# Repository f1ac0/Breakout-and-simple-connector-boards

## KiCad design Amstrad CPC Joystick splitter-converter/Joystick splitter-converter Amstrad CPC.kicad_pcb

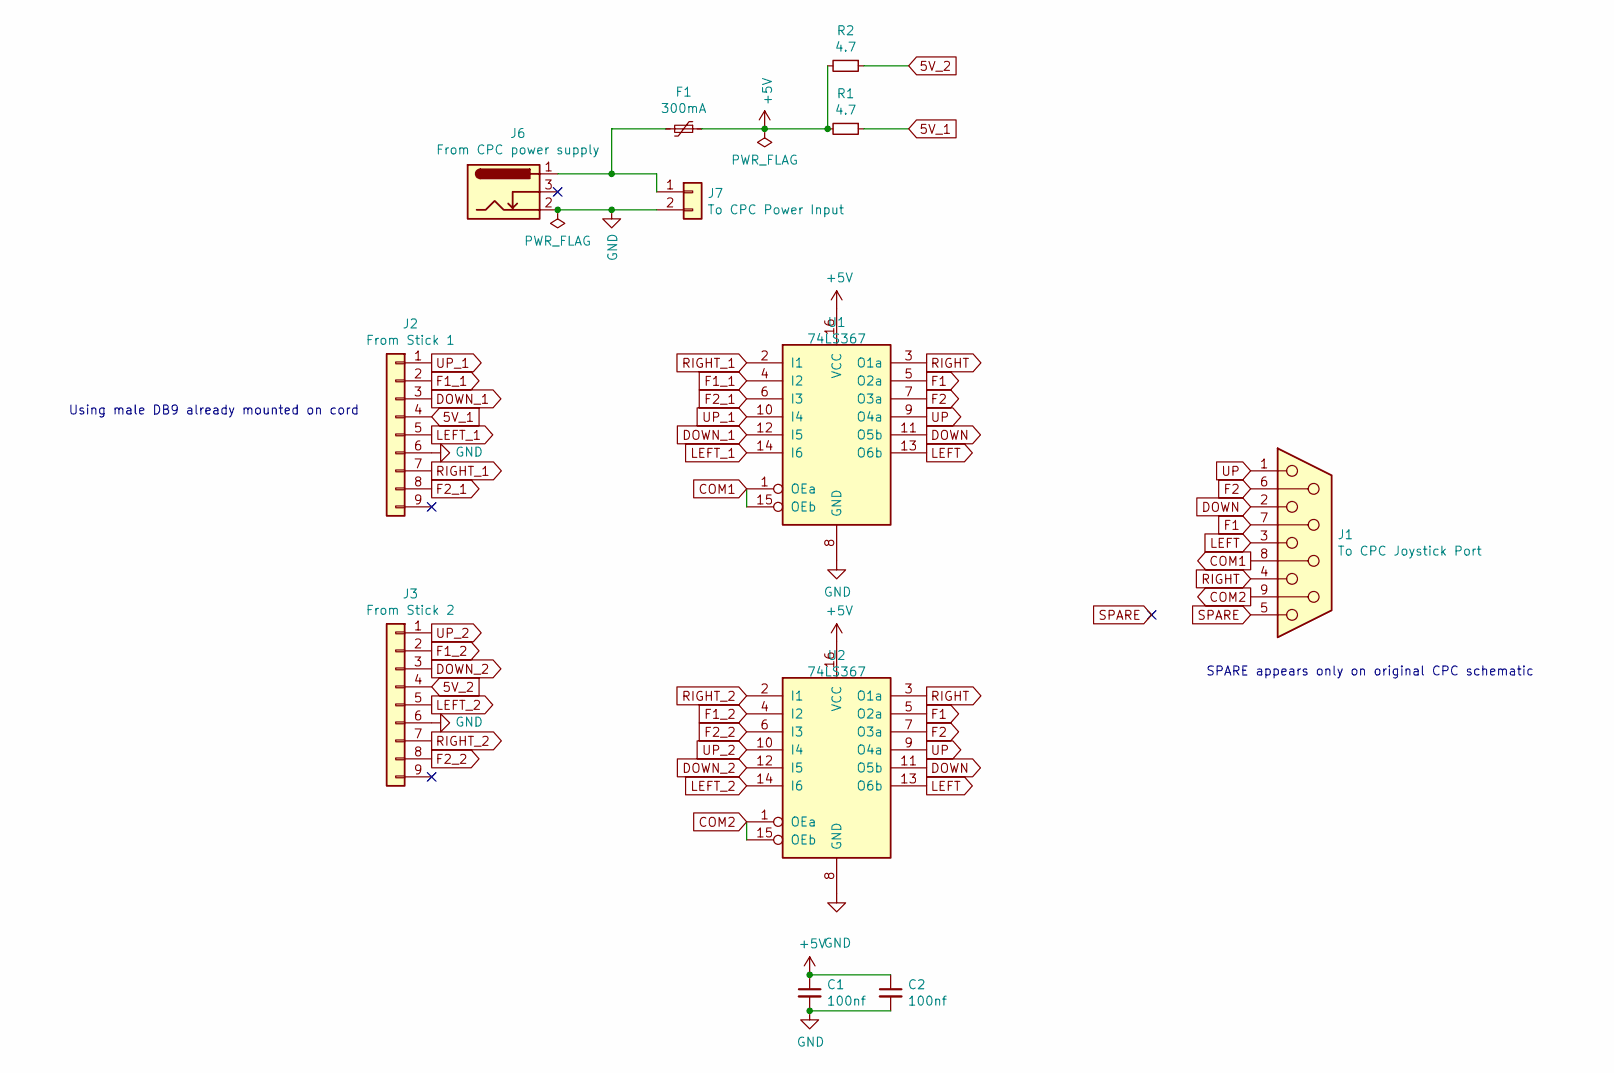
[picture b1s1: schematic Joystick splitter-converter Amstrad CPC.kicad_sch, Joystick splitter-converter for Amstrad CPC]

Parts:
C1, C2: 100nf; C_Disc_D3.0mm_W2.0mm_P2.50mm
F1: 300mA; C_Disc_D4.3mm_W1.9mm_P5.00mm
J1: To CPC Joystick Port; DSUB-9_Female_EdgeMount_P2.77mm
J2: From Stick 1; PinHeader_2x05_P2.54mm_Vertical
J3: From Stick 2; PinHeader_2x05_P2.54mm_Vertical
J6: From CPC power supply; BarrelJack_Horizontal
J7: To CPC Power Input; SolderWire-1.5sqmm_1x02_P6mm_D1.7mm_OD3mm
R1, R2: 4.7; R_Axial_DIN0207_L6.3mm_D2.5mm_P15.24mm_Horizontal
U1, U2: 74LS367; DIP-16_W7.62mm

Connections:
5V_1: J2.4, R1.1
5V_2: J3.4, R2.1
+5V: C1.1, C2.1, F1.1, R1.2, R2.2, U1.16 (VCC), U2.16 (VCC)
COM1: J1.8, U1.1 (OEa), U1.15 (OEb)
COM2: J1.9, U2.1 (OEa), U2.15 (OEb)
DOWN: J1.2, U1.11 (O5b), U2.11 (O5b)
DOWN_1: J2.3, U1.12 (I5)
DOWN_2: J3.3, U2.12 (I5)
F1: J1.7, U1.5 (O2a), U2.5 (O2a)
F1_1: J2.2, U1.4 (I2)
F1_2: J3.2, U2.4 (I2)
F2: J1.6, U1.7 (O3a), U2.7 (O3a)
F2_1: J2.8, U1.6 (I3)
F2_2: J3.8, U2.6 (I3)
GND: C1.2, C2.2, J2.6, J3.6, J6.2, J7.2, U1.8 (GND), U2.8 (GND)
LEFT: J1.3, U1.13 (O6b), U2.13 (O6b)
LEFT_1: J2.5, U1.14 (I6)
LEFT_2: J3.5, U2.14 (I6)
unnamed: F1.2, J6.1, J7.1
RIGHT: J1.4, U1.3 (O1a), U2.3 (O1a)
RIGHT_1: J2.7, U1.2 (I1)
RIGHT_2: J3.7, U2.2 (I1)
SPARE: J1.5
UP: J1.1, U1.9 (O4a), U2.9 (O4a)
UP_1: J2.1, U1.10 (I4)
UP_2: J3.1, U2.10 (I4)

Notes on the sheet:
Using male DB9 already mounted on cord
SPARE appears only on original CPC schematic

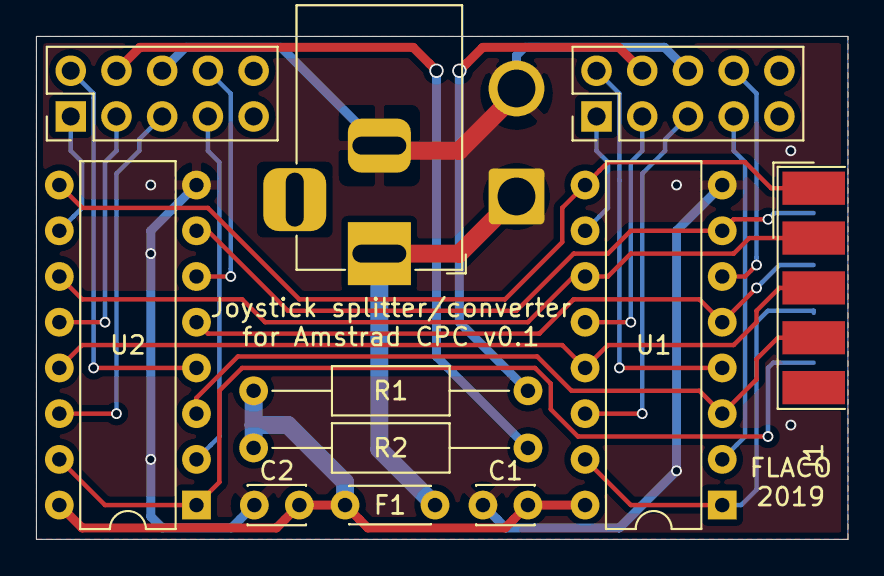
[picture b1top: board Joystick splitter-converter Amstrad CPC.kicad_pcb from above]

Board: 2 copper layers, 45.1 x 27.9 mm, 12 parts (0 on the bottom side), 25 nets.

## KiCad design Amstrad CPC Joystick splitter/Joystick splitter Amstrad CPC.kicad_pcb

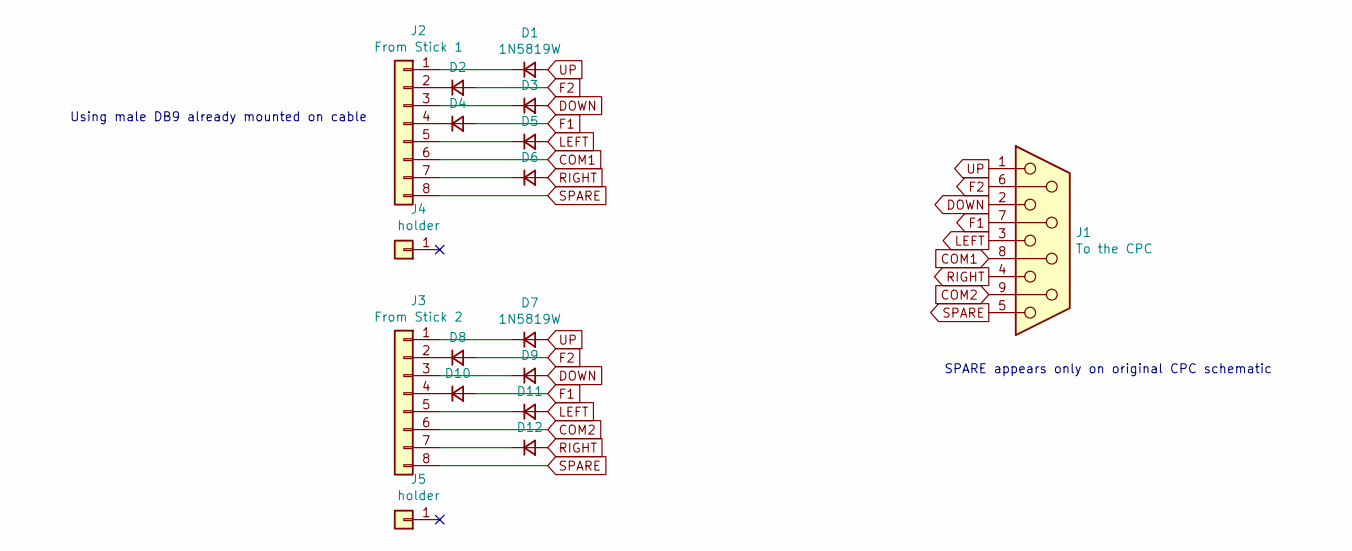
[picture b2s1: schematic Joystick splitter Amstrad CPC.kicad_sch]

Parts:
D1, D2, D3, D4, D5, D6, D7, D8, D9, D10, D11, D12: 1N5819W; D_SOD-123
J1: To the CPC; DSUB-9_Female_EdgeMount_P2.77mm
J2: From Stick 1; PinHeader_1x08_P2.54mm_Vertical
J3: From Stick 2; PinHeader_1x08_P2.54mm_Vertical
J4, J5: holder; PinHeader_1x01_P2.54mm_Vertical

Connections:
COM1: J1.8, J2.6
COM2: J1.9, J3.6
DOWN: D3.2 (A), D9.2 (A), J1.2
F1: D4.2 (A), D10.2 (A), J1.7
F2: D2.2 (A), D8.2 (A), J1.6
LEFT: D5.2 (A), D11.2 (A), J1.3
unnamed: D1.1 (K), J2.1
unnamed: D2.1 (K), J2.2
unnamed: D3.1 (K), J2.3
unnamed: D4.1 (K), J2.4
unnamed: D5.1 (K), J2.5
unnamed: D6.1 (K), J2.7
unnamed: D7.1 (K), J3.1
unnamed: D8.1 (K), J3.2
unnamed: D9.1 (K), J3.3
unnamed: D10.1 (K), J3.4
unnamed: D11.1 (K), J3.5
unnamed: D12.1 (K), J3.7
RIGHT: D6.2 (A), D12.2 (A), J1.4
SPARE: J1.5, J2.8, J3.8
UP: D1.2 (A), D7.2 (A), J1.1

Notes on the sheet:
SPARE appears only on original CPC schematic
Using male DB9 already mounted on cable

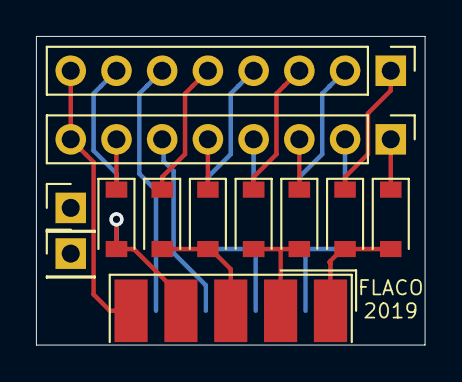
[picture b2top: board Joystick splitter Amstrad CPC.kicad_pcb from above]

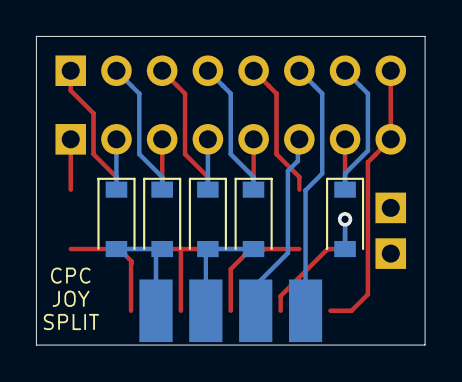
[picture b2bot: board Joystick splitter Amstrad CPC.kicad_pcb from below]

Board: 2 copper layers, 21.6 x 17.1 mm, 17 parts (5 on the bottom side), 21 nets.

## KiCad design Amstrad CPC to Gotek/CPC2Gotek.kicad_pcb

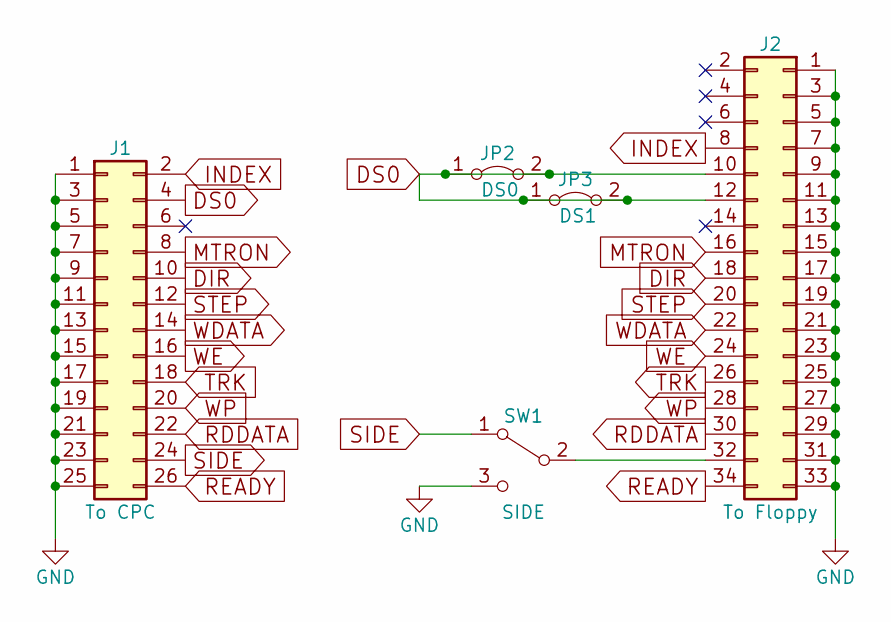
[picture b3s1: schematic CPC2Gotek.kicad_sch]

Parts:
J1: To CPC; Pin_Header_2x13_Male_EdgeMount_Pitch2.54mm
J2: To Floppy; Pin_Header_2x17_Female_EdgeMount_Pitch2.54mm
JP2: DS0; SOLDER-JUMPER_1-WAY-CLOSED
JP3: DS1; SOLDER-JUMPER_1-WAY-CLOSED
SW1: SIDE; PinSocket_1x03_P2.54mm_Vertical

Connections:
DIR: J1.10, J2.18
DS0: J1.4, J2.10, J2.12, JP2.1 (A), JP2.2 (B), JP3.1 (A), JP3.2 (B)
GND: J1.1, J1.3, J1.5, J1.7, J1.9, J1.11, J1.13, J1.15, J1.17, J1.19, J1.21, J1.23, J1.25, J2.1, J2.3, J2.5, J2.7, J2.9, J2.11, J2.13, J2.15, J2.17, J2.19, J2.21, J2.23, J2.25, J2.27, J2.29, J2.31, J2.33, SW1.3 (C)
INDEX: J1.2, J2.8
MTRON: J1.8, J2.16
unnamed: J2.32, SW1.2 (B)
RDDATA: J1.22, J2.30
READY: J1.26, J2.34
SIDE: J1.24, SW1.1 (A)
STEP: J1.12, J2.20
TRK: J1.18, J2.26
WDATA: J1.14, J2.22
WE: J1.16, J2.24
WP: J1.20, J2.28

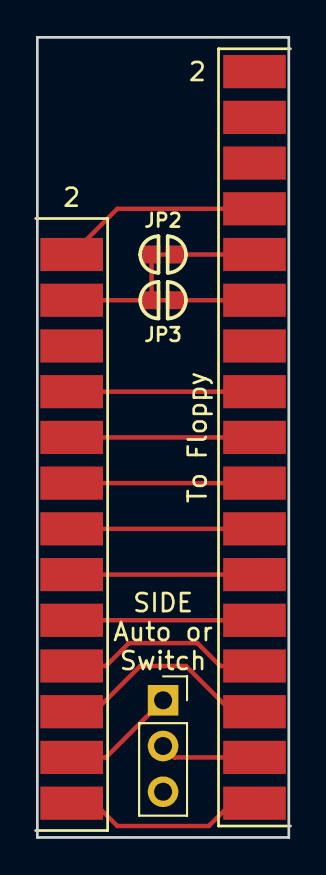
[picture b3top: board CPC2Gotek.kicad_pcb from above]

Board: 2 copper layers, 14.0 x 44.5 mm, 5 parts (0 on the bottom side), 14 nets.

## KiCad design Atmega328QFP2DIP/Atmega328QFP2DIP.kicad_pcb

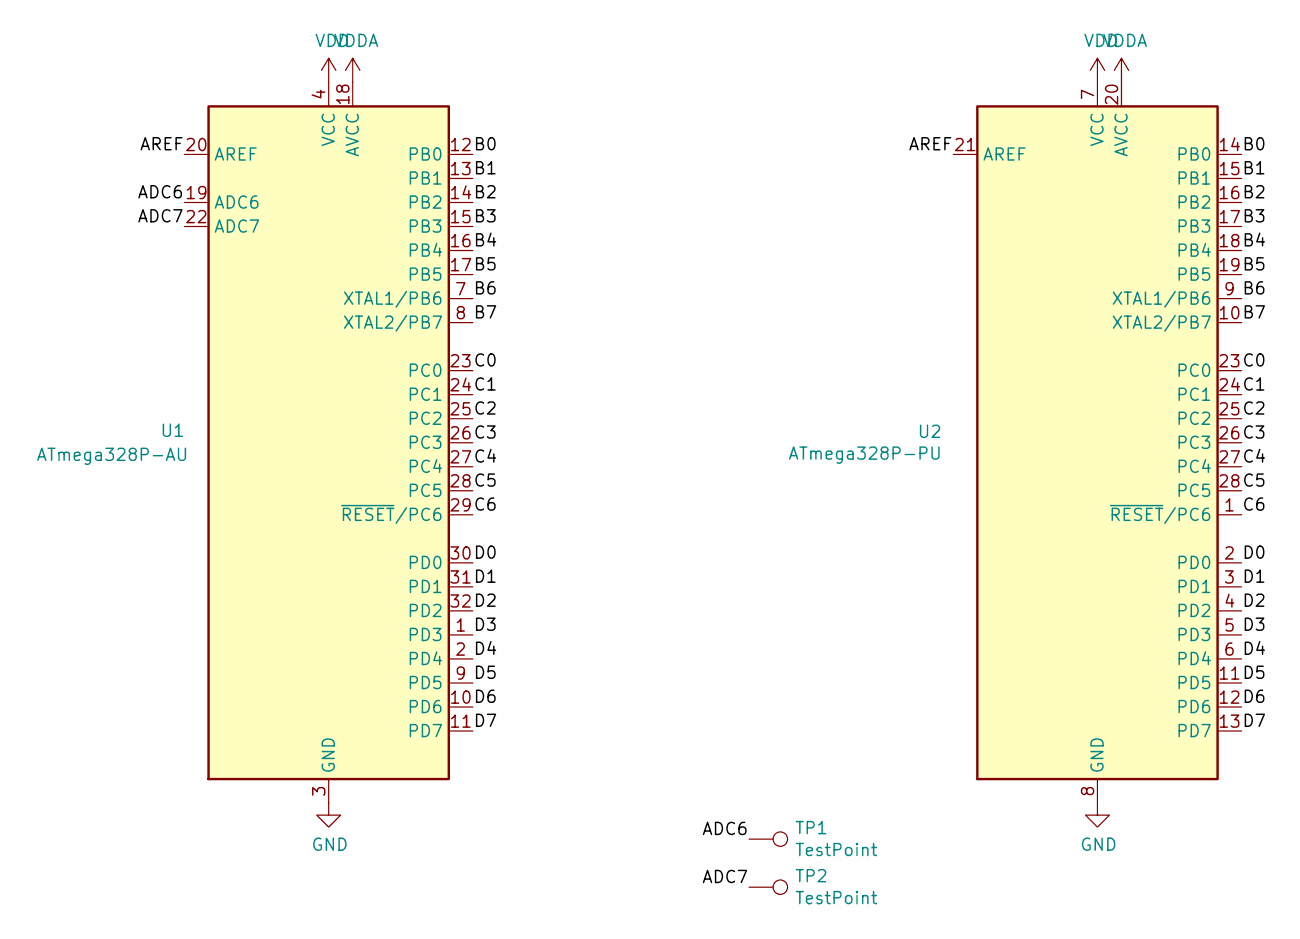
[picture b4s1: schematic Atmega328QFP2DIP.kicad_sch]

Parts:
TP1, TP2: TestPoint; Pin_THT_Square_Pitch2.54mm
U1: ATmega328P-AU; TQFP-32_7x7mm_P0.8mm
U2: ATmega328P-PU; DIP-28_W15.24mm

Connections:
/ADC6: TP1.1, U1.19 (ADC6)
/ADC7: TP2.1, U1.22 (ADC7)
/AREF: U1.20 (AREF), U2.21 (AREF)
/B0: U1.12 (PB0), U2.14 (PB0)
/B1: U1.13 (PB1), U2.15 (PB1)
/B2: U1.14 (PB2), U2.16 (PB2)
/B3: U1.15 (PB3), U2.17 (PB3)
/B4: U1.16 (PB4), U2.18 (PB4)
/B5: U1.17 (PB5), U2.19 (PB5)
/B6: U1.7 (XTAL1/PB6), U2.9 (XTAL1/PB6)
/B7: U1.8 (XTAL2/PB7), U2.10 (XTAL2/PB7)
/C0: U1.23 (PC0), U2.23 (PC0)
/C1: U1.24 (PC1), U2.24 (PC1)
/C2: U1.25 (PC2), U2.25 (PC2)
/C3: U1.26 (PC3), U2.26 (PC3)
/C4: U1.27 (PC4), U2.27 (PC4)
/C5: U1.28 (PC5), U2.28 (PC5)
/C6: U1.29 (~RESET/PC6), U2.1 (~RESET/PC6)
/D0: U1.30 (PD0), U2.2 (PD0)
/D1: U1.31 (PD1), U2.3 (PD1)
/D2: U1.32 (PD2), U2.4 (PD2)
/D3: U1.1 (PD3), U2.5 (PD3)
/D4: U1.2 (PD4), U2.6 (PD4)
/D5: U1.9 (PD5), U2.11 (PD5)
/D6: U1.10 (PD6), U2.12 (PD6)
/D7: U1.11 (PD7), U2.13 (PD7)
GND: U1.3 (GND), U1.5 (GND), U1.21 (GND), U2.8 (GND), U2.22 (GND)
VDD: U1.4 (VCC), U1.6 (VCC), U2.7 (VCC)
VDDA: U1.18 (AVCC), U2.20 (AVCC)

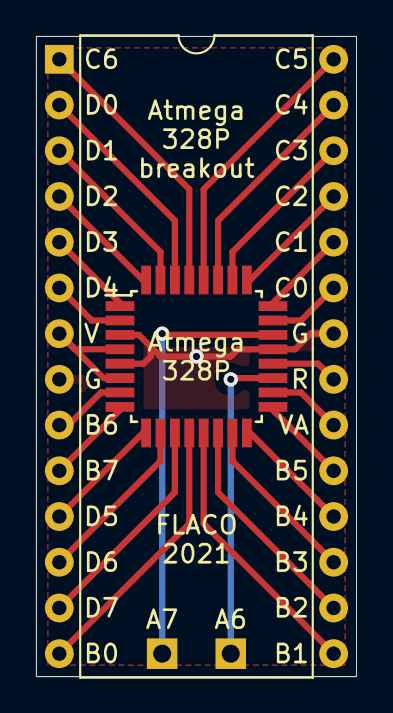
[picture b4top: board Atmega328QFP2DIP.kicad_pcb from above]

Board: 2 copper layers, 17.8 x 35.6 mm, 4 parts (0 on the bottom side), 29 nets.

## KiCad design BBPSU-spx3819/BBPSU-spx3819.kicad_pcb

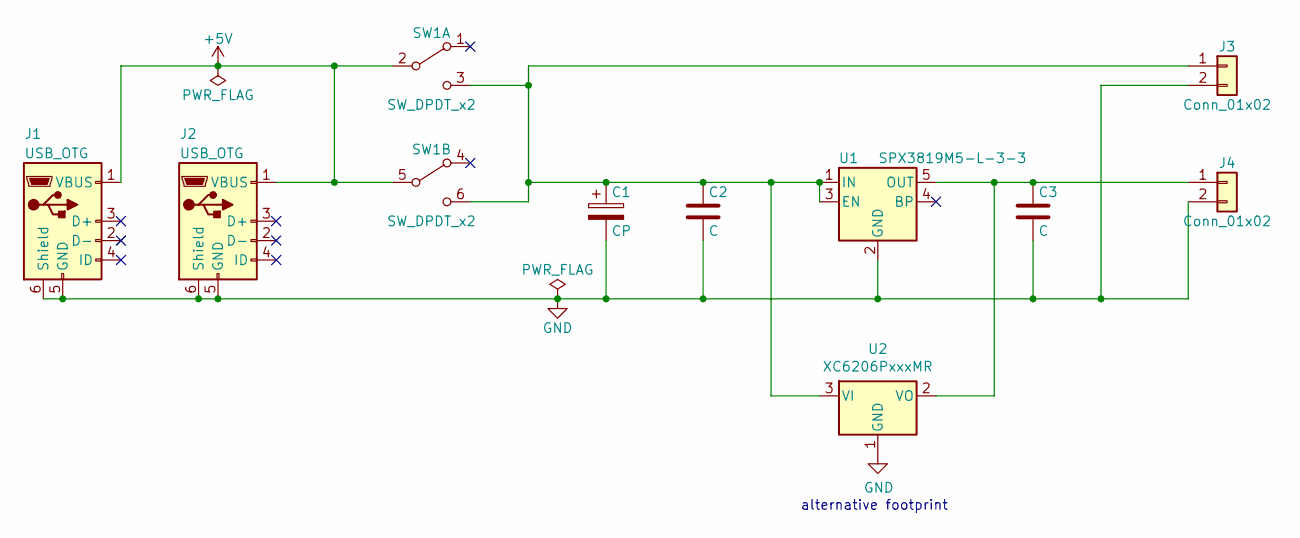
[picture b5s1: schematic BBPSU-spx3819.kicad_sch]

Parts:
C1: CP; CP_Radial_D6.3mm_P2.50mm
C2, C3: C; C_0805_2012Metric_Pad1.18x1.45mm_HandSolder
J1: USB_OTG; USB-MICRO-B
J2: USB_OTG; USB_Mini-B_Wuerth_65100516121_Horizontal
J3, J4: Conn_01x02; PinHeader_1x02_P2.54mm_Vertical
SW1: SW_DPDT_x2; SW_PUSH_Self-locking_5.8mm
U1: SPX3819M5-L-3-3; SOT-23-5_HandSoldering
U2: XC6206PxxxMR; SOT-23

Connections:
+5V: J1.1 (VBUS), J2.1 (VBUS), SW1.2 (B), SW1.5 (B)
GND: C1.2, C2.2, C3.2, J1.5 (GND), J1.6 (Shield), J2.5 (GND), J2.6 (Shield), J3.2, J4.2, U1.2 (GND), U2.1 (GND)
unnamed: C1.1, C2.1, J3.1, SW1.3 (C), SW1.6 (C), U1.1 (IN), U1.3 (EN), U2.3 (VI)
unnamed: C3.1, J4.1, U1.5 (OUT), U2.2 (VO)

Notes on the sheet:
alternative footprint

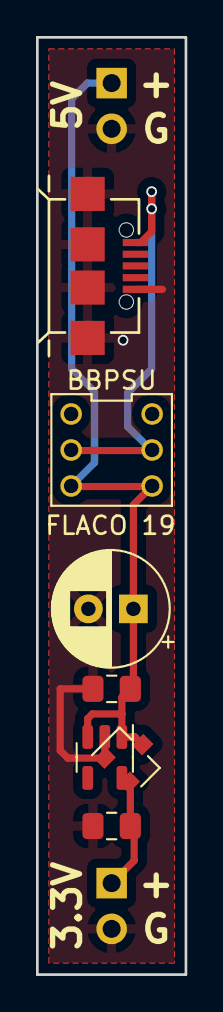
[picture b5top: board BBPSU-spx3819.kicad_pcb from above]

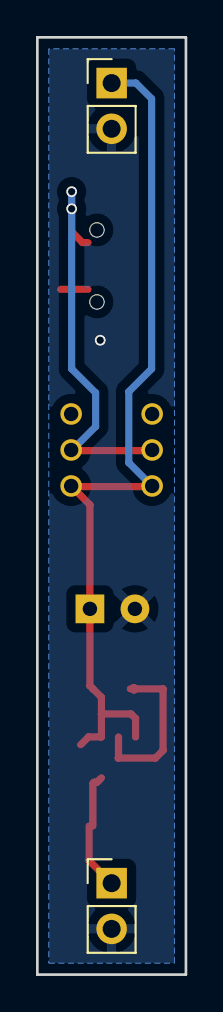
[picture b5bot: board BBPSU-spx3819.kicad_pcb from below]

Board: 2 copper layers, 8.3 x 52.1 mm, 9 parts (2 on the bottom side), 4 nets.

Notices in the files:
Amstrad CPC to Gotek/CPC2Gotek.kicad_pcb:
FLACO 2018, licence of this schematic is CC-BY-NC-SA
BBPSU-spx3819/BBPSU-spx3819.kicad_pcb:
FLACO 2017, licence of this PCB is CC-BY-NC-SA
BBPSU-spx3819/BBPSU-spx3819.kicad_sch:
FLACO 2017, licence of this schematic is CC-BY-NC-SA
